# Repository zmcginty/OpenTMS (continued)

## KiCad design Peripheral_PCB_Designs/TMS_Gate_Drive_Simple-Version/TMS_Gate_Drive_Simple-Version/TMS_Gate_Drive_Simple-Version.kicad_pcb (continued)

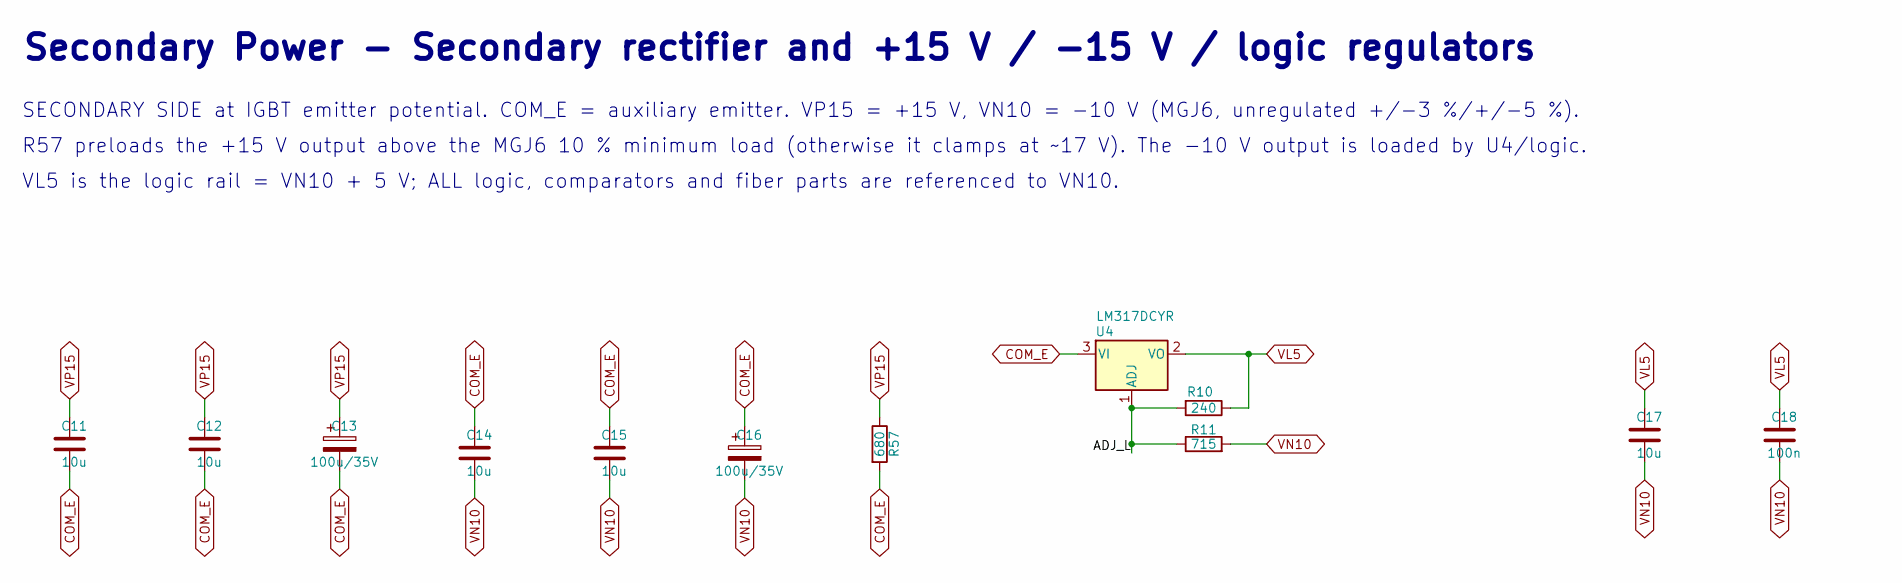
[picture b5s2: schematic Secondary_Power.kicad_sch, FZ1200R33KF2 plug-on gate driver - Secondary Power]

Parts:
C11, C12, C14, C15, C17: 10u; C_1210_3225Metric; MPN GRM32ER71H106KA12L
C13, C16: 100u/35V; CP_Elec_8x10; MPN EEE-FK1V101P
C18: 100n; C_0603_1608Metric; MPN GCM188R71H104KA57D
R10: 240; R_0603_1608Metric; MPN RC0603FR-07240L
R11: 715; R_0603_1608Metric; MPN RC0603FR-07715L
R57: 680; R_2512_6332Metric; MPN CRCW2512680RFKEG
U4: LM317DCYR; SOT-223-3_TabPin2; MPN LM317DCYR

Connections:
/Secondary_Power/ADJ_L: R10.2, R11.1, U4.1 (ADJ)
COM_E: C11.2, C12.2, C13.2, C14.1, C15.1, C16.1, R57.2, U4.3 (VI); also elsewhere on the board
VL5: C17.1, C18.1, R10.1, U4.2 (VO); also elsewhere on the board
VN10: C14.2, C15.2, C16.2, C17.2, C18.2, R11.2; also elsewhere on the board
VP15: C11.1, C12.1, C13.1, R57.1; also elsewhere on the board

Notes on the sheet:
Secondary Power - Secondary rectifier and +15 V / -15 V / logic regulators
SECONDARY SIDE at IGBT emitter potential. COM_E = auxiliary emitter. VP15 = +15 V, VN10 = -10 V (MGJ6, unregulated +/-3 %/+/-5 %).
R57 preloads the +15 V output above the MGJ6 10 % minimum load (otherwise it clamps at ~17 V). The -10 V output is loaded by U4/logic.
VL5 is the logic rail = VN10 + 5 V; ALL logic, comparators and fiber parts are referenced to VN10.

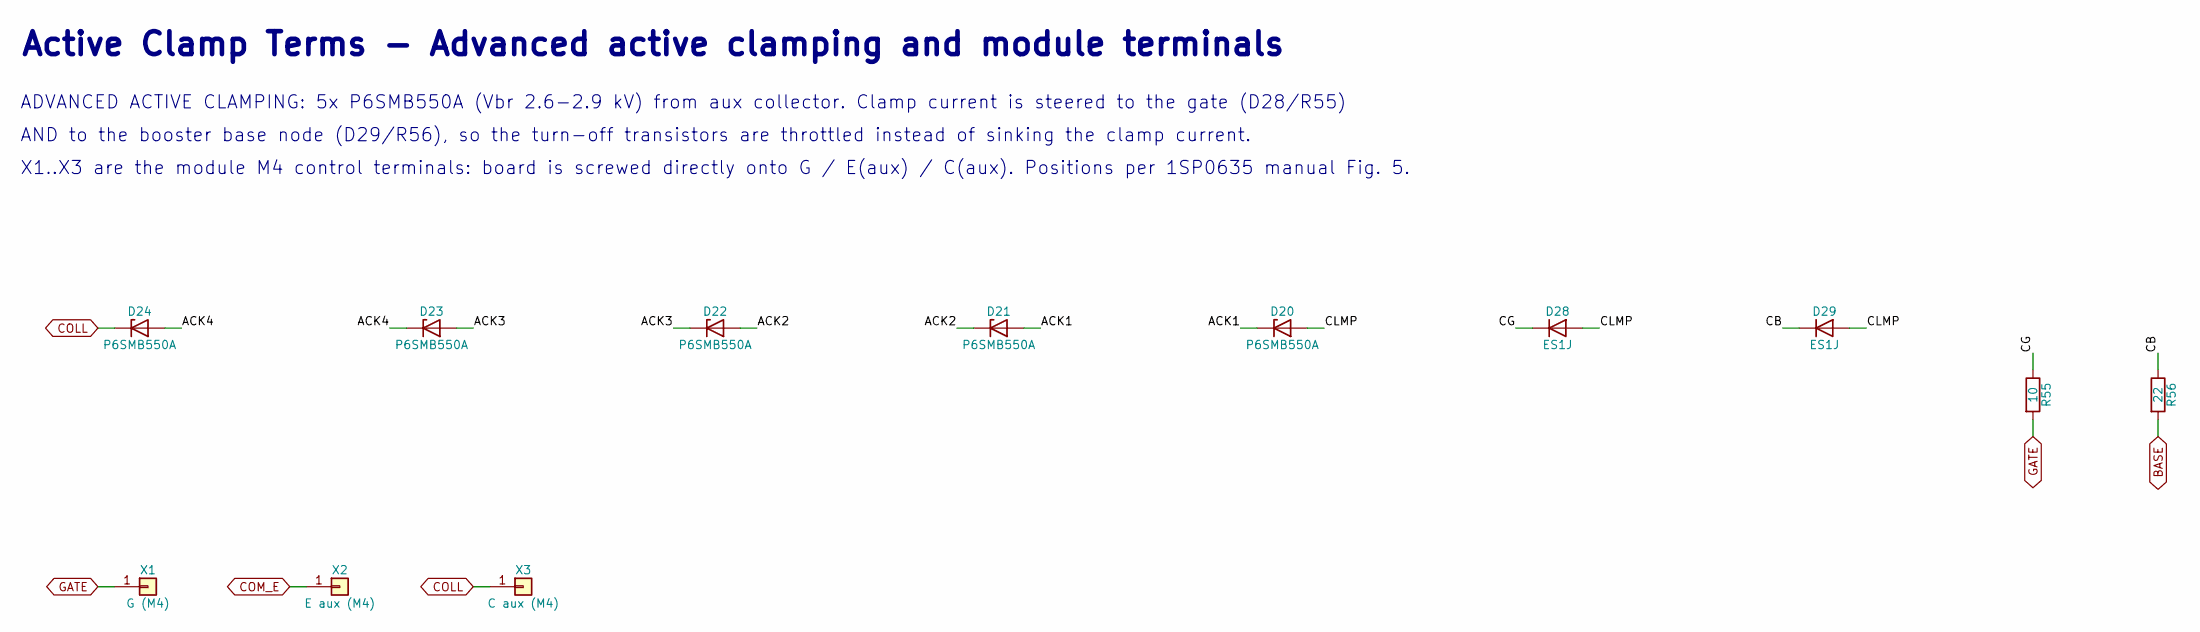
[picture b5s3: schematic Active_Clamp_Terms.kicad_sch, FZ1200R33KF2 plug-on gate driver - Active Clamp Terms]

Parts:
D20, D21, D22, D23, D24: P6SMB550A; D_SMB; MPN P6SMB550A
D28, D29: ES1J; D_SMA; MPN ES1J-E3/61T
R55: 10; R_2512_6332Metric; MPN CRCW251210R0FKEG
R56: 22; R_1206_3216Metric; MPN RC1206FR-0722L
X1: G (M4); IHV_AuxTerminal_M4; MPN M4 screw
X2: E aux (M4); IHV_AuxTerminal_M4; MPN M4 screw
X3: C aux (M4); IHV_AuxTerminal_M4; MPN M4 screw

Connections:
/Active_Clamp_Terms/ACK1: D20.1 (K), D21.2 (A)
/Active_Clamp_Terms/ACK2: D21.1 (K), D22.2 (A)
/Active_Clamp_Terms/ACK3: D22.1 (K), D23.2 (A)
/Active_Clamp_Terms/ACK4: D23.1 (K), D24.2 (A)
/Active_Clamp_Terms/CB: D29.1 (K), R56.1
/Active_Clamp_Terms/CG: D28.1 (K), R55.1
/Active_Clamp_Terms/CLMP: D20.2 (A), D28.2 (A), D29.2 (A)
BASE: R56.2; also elsewhere on the board
COLL: D24.1 (K), X3.1 (Pin_1_1); also elsewhere on the board
COM_E: X2.1 (Pin_1_1); also elsewhere on the board
GATE: R55.2, X1.1 (Pin_1_1); also elsewhere on the board

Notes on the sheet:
X1..X3 are the module M4 control terminals: board is screwed directly onto G / E(aux) / C(aux). Positions per 1SP0635 manual Fig. 5.
ADVANCED ACTIVE CLAMPING: 5x P6SMB550A (Vbr 2.6-2.9 kV) from aux collector. Clamp current is steered to the gate (D28/R55)
AND to the booster base node (D29/R56), so the turn-off transistors are throttled instead of sinking the clamp current.
Active Clamp Terms - Advanced active clamping and module terminals

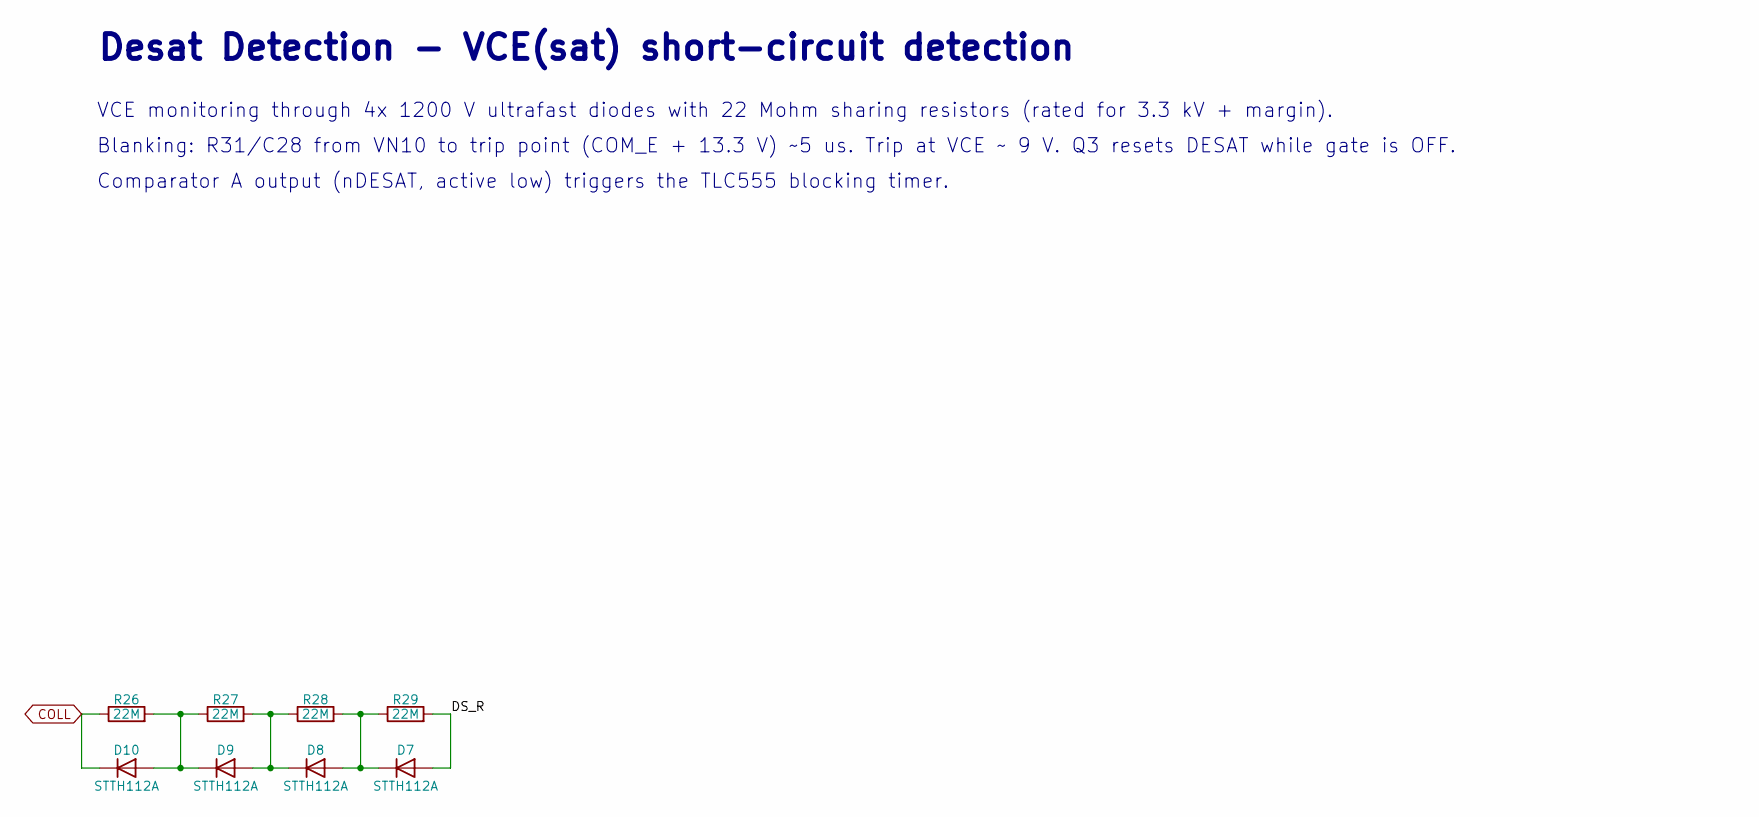
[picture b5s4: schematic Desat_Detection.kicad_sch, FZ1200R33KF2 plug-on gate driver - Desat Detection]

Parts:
D7, D8, D9, D10: STTH112A; D_SMA; MPN STTH112A
R26, R27, R28, R29: 22M; R_2512_6332Metric; MPN HVC2512T2205FET

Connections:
/Desat_Detection/DS_R: D7.2 (A), R29.2
COLL: D10.1 (K), R26.1; also elsewhere on the board
unnamed: D7.1 (K), D8.2 (A), R28.2, R29.1
unnamed: D8.1 (K), D9.2 (A), R27.2, R28.1
unnamed: D9.1 (K), D10.2 (A), R26.2, R27.1

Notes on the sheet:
Comparator A output (nDESAT, active low) triggers the TLC555 blocking timer.
VCE monitoring through 4x 1200 V ultrafast diodes with 22 Mohm sharing resistors (rated for 3.3 kV + margin).
Desat Detection - VCE(sat) short-circuit detection
Blanking: R31/C28 from VN10 to trip point (COM_E + 13.3 V) ~5 us. Trip at VCE ~ 9 V. Q3 resets DESAT while gate is OFF.

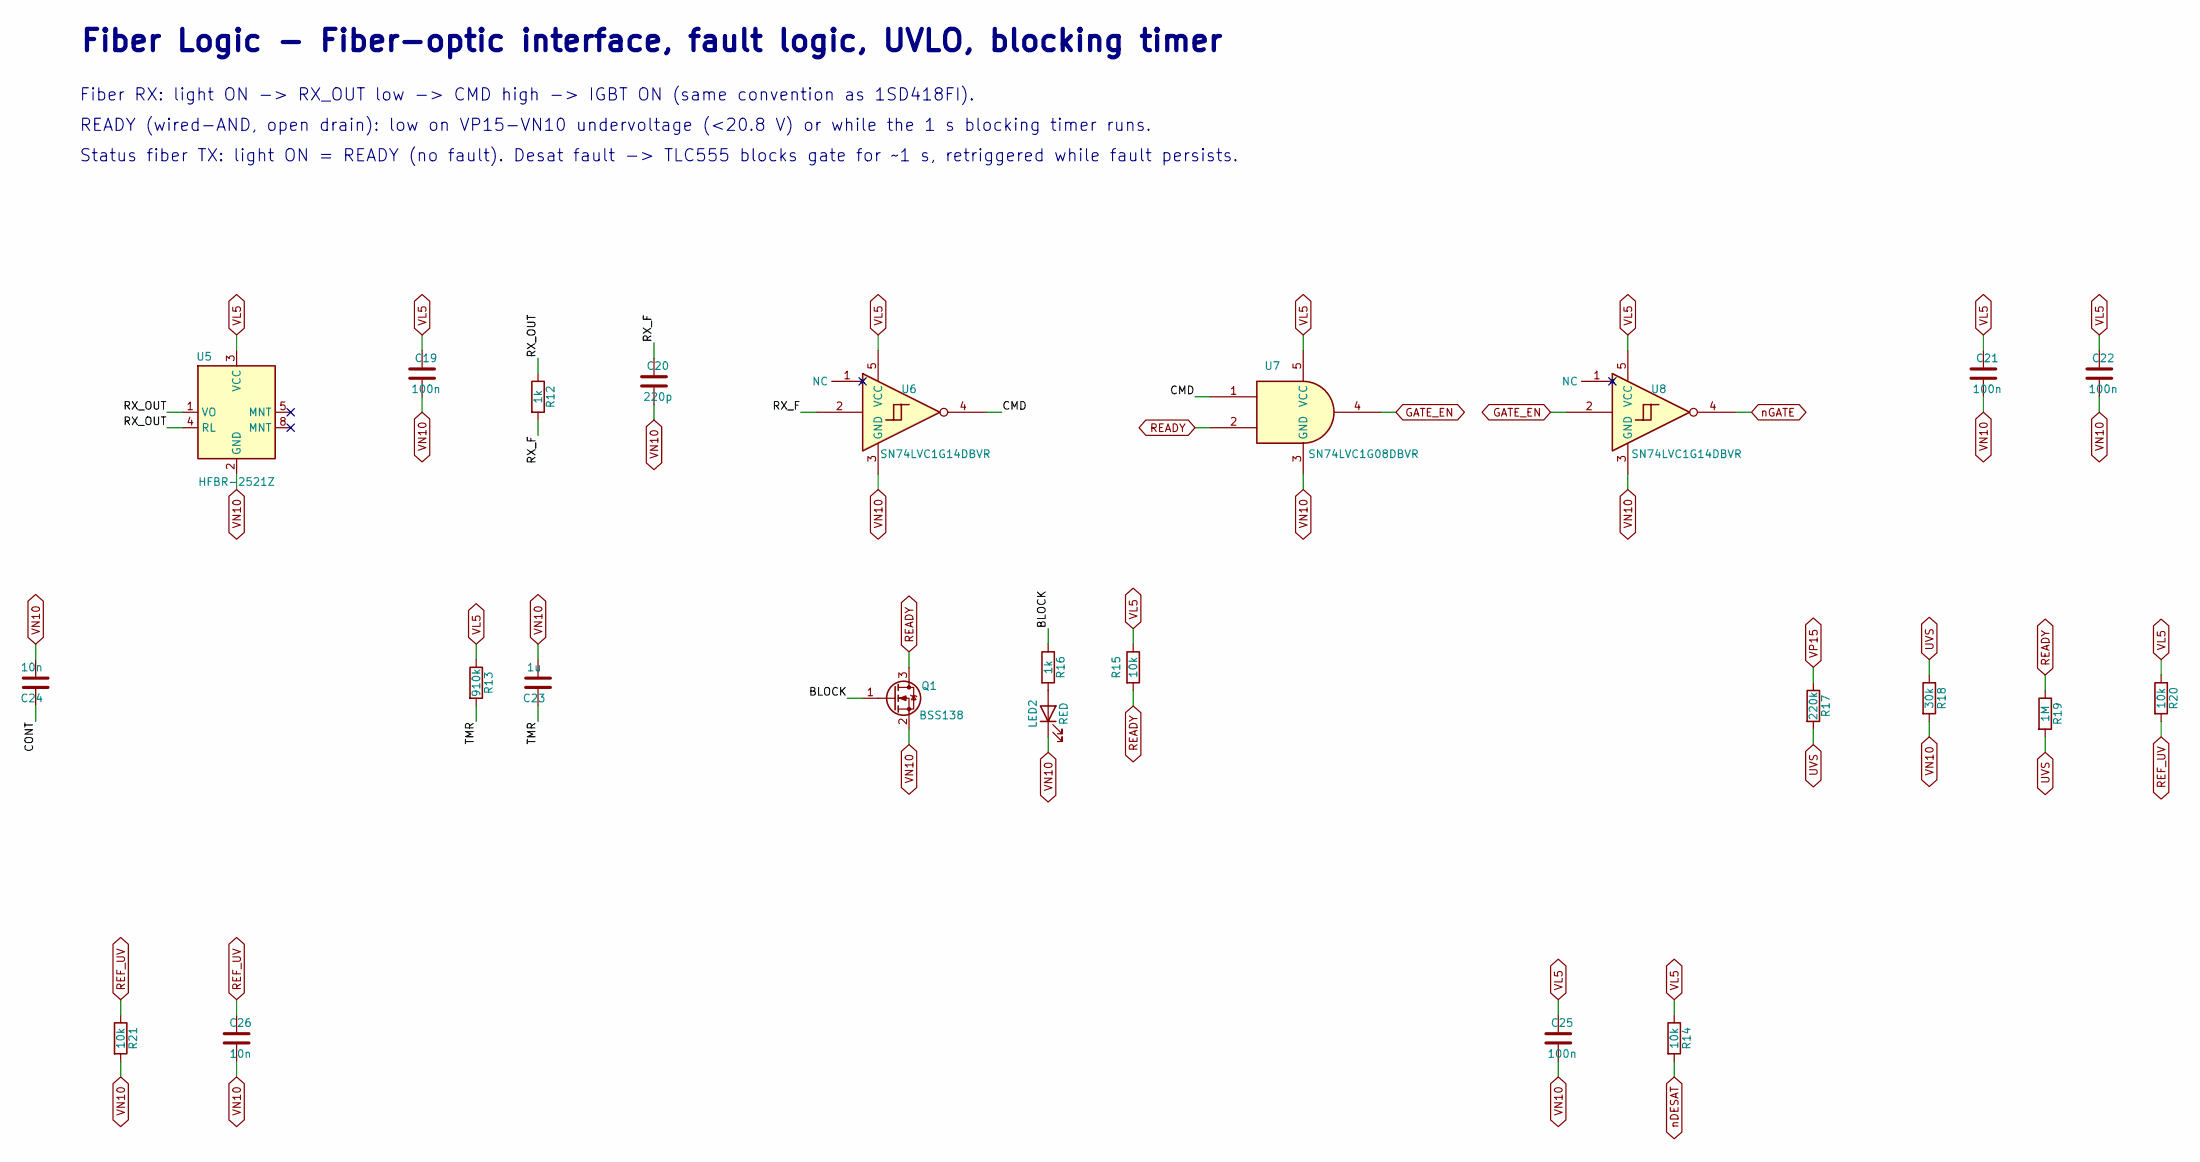
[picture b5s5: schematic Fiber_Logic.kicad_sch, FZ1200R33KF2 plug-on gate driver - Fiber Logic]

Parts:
C19, C21, C22, C25: 100n; C_0603_1608Metric; MPN GCM188R71H104KA57D
C20: 220p; C_0603_1608Metric; MPN GRM1885C1H221JA01D
C23: 1u; C_0805_2012Metric; MPN GRM21BR71H105KA12L
C24, C26: 10n; C_0603_1608Metric; MPN GCM188R71H103KA37D
LED2: RED; LED_0603_1608Metric; MPN 150060RS75000
Q1: BSS138; SOT-23; MPN BSS138
R12, R16: 1k; R_0603_1608Metric; MPN RC0603FR-071kL
R13: 910k; R_0603_1608Metric; MPN RC0603FR-07910kL
R14, R15, R20, R21: 10k; R_0603_1608Metric; MPN RC0603FR-0710kL
R17: 220k; R_0603_1608Metric; MPN RC0603FR-07220kL
R18: 30k; R_0603_1608Metric; MPN RC0603FR-0730kL
R19: 1M; R_0603_1608Metric; MPN RC0603FR-071ML
U5: HFBR-2521Z; Broadcom_VersatileLink_Horizontal; MPN HFBR-2521Z
U6, U8: SN74LVC1G14DBVR; SOT-23-5; MPN SN74LVC1G14DBVR
U7: SN74LVC1G08DBVR; SOT-23-5; MPN SN74LVC1G08DBVR

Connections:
/Fiber_Logic/BLOCK: Q1.1 (G), R16.1
/Fiber_Logic/CMD: U6.4, U7.1
/Fiber_Logic/CONT: C24.1
/Fiber_Logic/RX_F: C20.1, R12.2, U6.2
/Fiber_Logic/RX_OUT: R12.1, U5.1 (VO), U5.4 (RL)
/Fiber_Logic/TMR: C23.1, R13.2
GATE_EN: U7.4, U8.2; also elsewhere on the board
unnamed: LED2.2 (A), R16.2
READY: Q1.3 (D), R15.2, R19.1, U7.2; also elsewhere on the board
REF_UV: C26.1, R20.2, R21.1
UVS: R17.2, R18.1, R19.2
VL5: C19.1, C21.1, C22.1, C25.1, R13.1, R14.1, R15.1, R20.1, U5.3 (VCC), U6.5 (VCC), U7.5 (VCC), U8.5 (VCC); also elsewhere on the board
VN10: C19.2, C20.2, C21.2, C22.2, C23.2, C24.2, C25.2, C26.2, LED2.1 (K), Q1.2 (S), R18.2, R21.2, U5.2 (GND), U6.3 (GND), U7.3 (GND), U8.3 (GND); also elsewhere on the board
VP15: R17.1; also elsewhere on the board
nDESAT: R14.2
nGATE: U8.4

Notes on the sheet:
Status fiber TX: light ON = READY (no fault). Desat fault -> TLC555 blocks gate for ~1 s, retriggered while fault persists.
READY (wired-AND, open drain): low on VP15-VN10 undervoltage (<20.8 V) or while the 1 s blocking timer runs.
Fiber RX: light ON -> RX_OUT low -> CMD high -> IGBT ON (same convention as 1SD418FI).
Fiber Logic - Fiber-optic interface, fault logic, UVLO, blocking timer

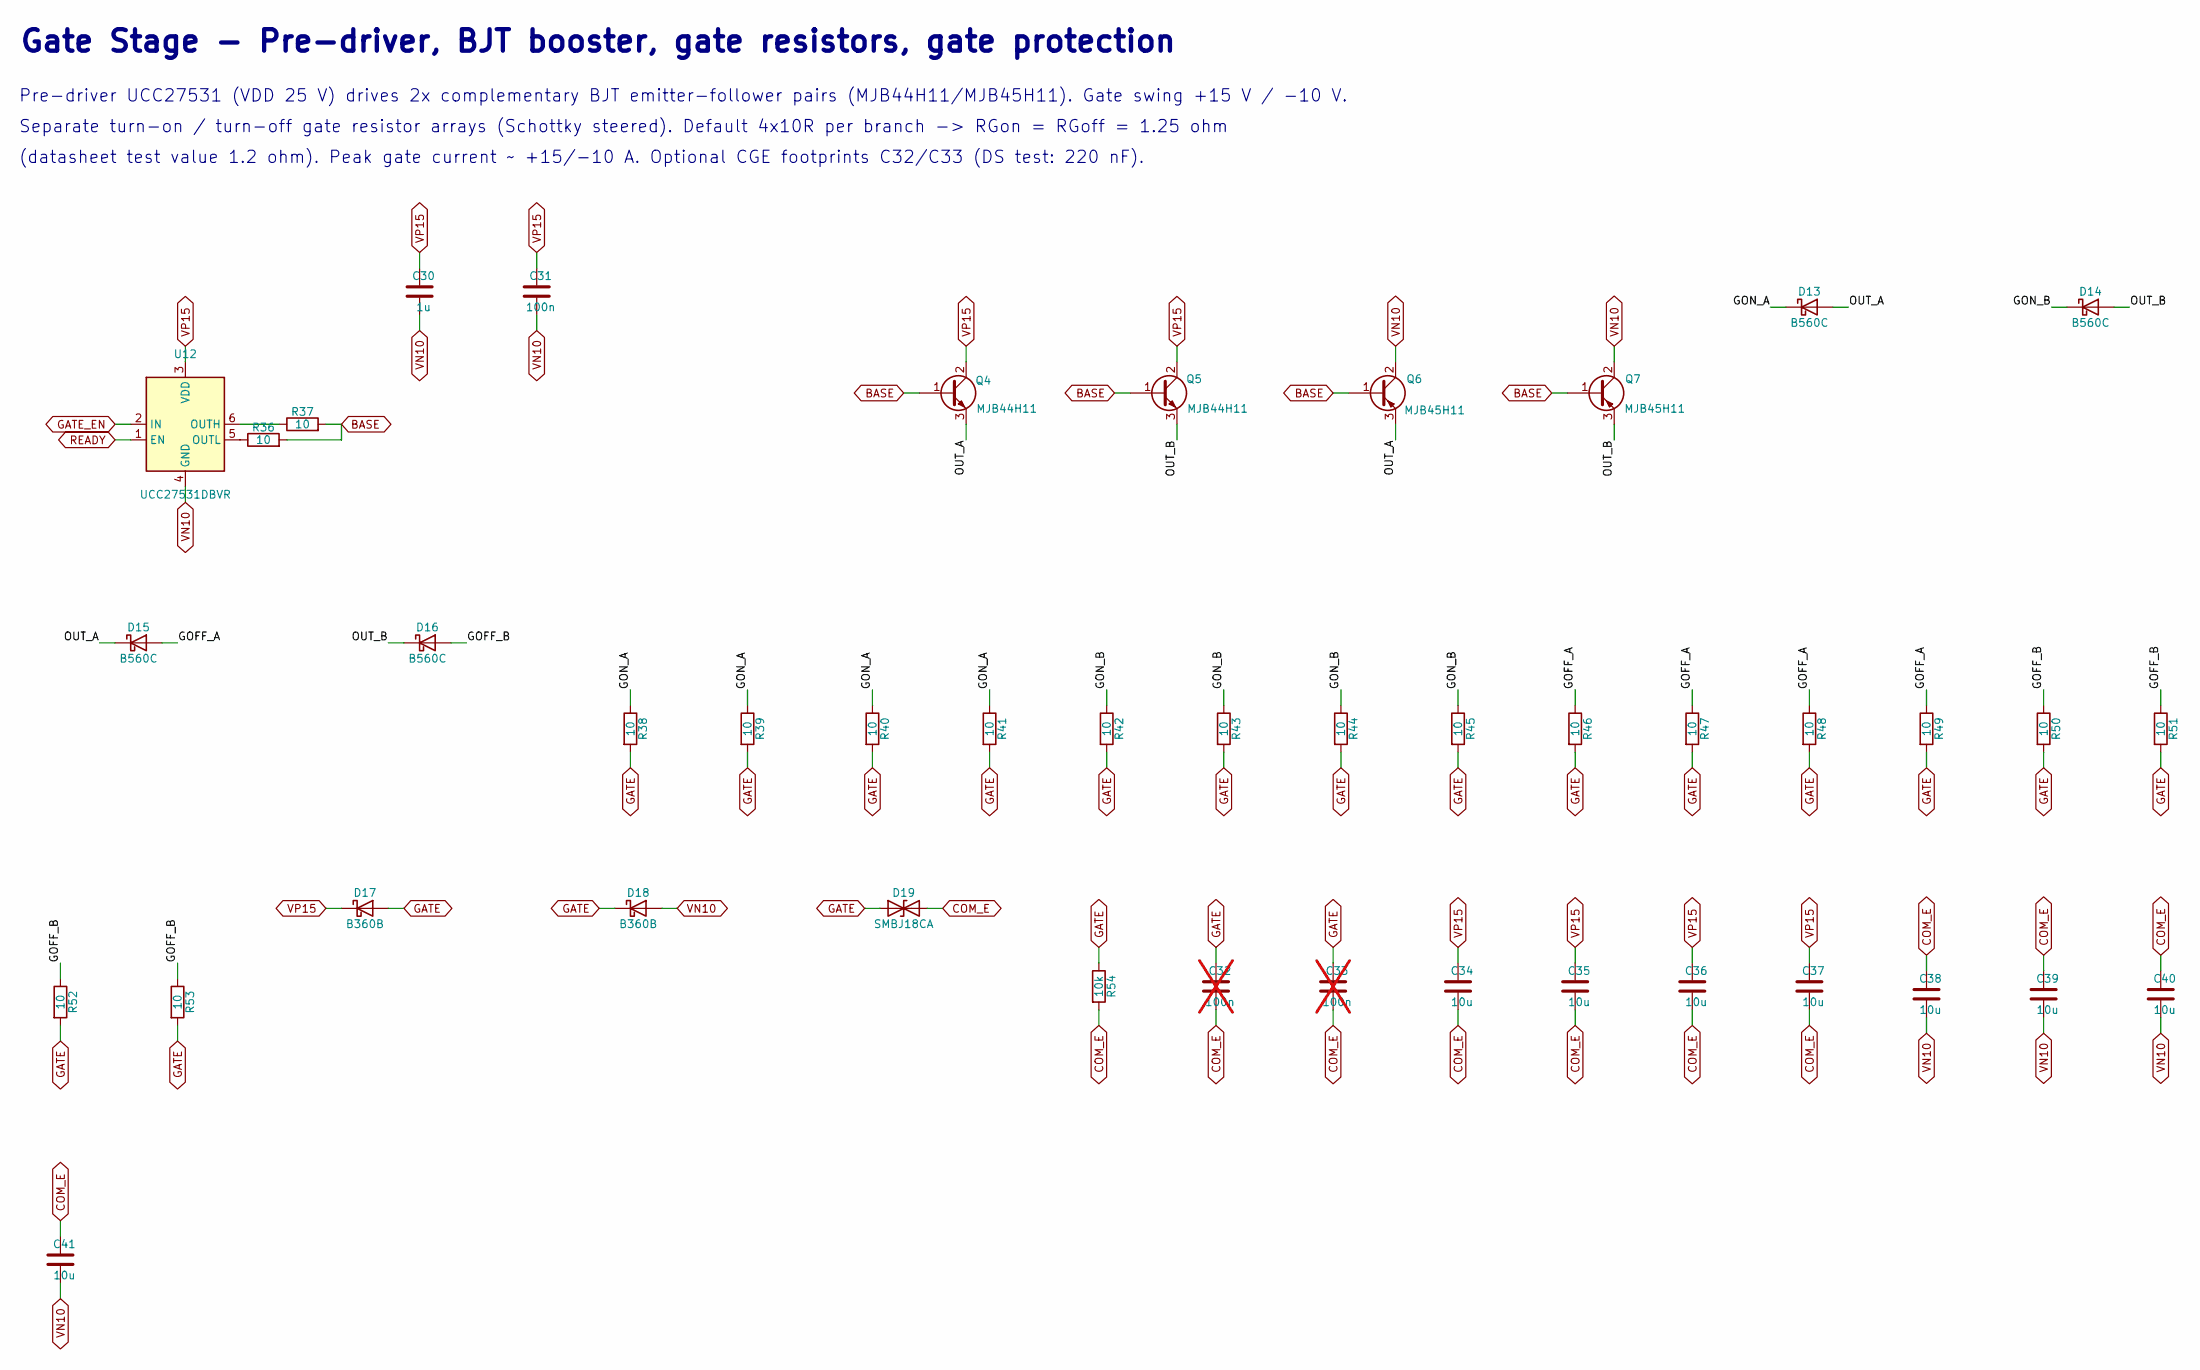
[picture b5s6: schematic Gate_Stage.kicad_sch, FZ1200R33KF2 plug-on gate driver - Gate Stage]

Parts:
C30: 1u; C_0805_2012Metric; MPN GRM21BR71H105KA12L
C31: 100n; C_0603_1608Metric; MPN GCM188R71H104KA57D
C32, C33: 100n; C_1210_3225Metric; MPN GCM32C5C1H104JA16L; not fitted
C34, C35, C36, C37, C38, C39, C40, C41: 10u; C_1210_3225Metric; MPN GRM32ER71H106KA12L
D13, D14, D15, D16: B560C; D_SMC; MPN B560C-13-F
D17, D18: B360B; D_SMB; MPN B360B-13-F
D19: SMBJ18CA; D_SMB; MPN SMBJ18CA
Q4, Q5: MJB44H11; TO-263-2; MPN MJB44H11T4G
Q6, Q7: MJB45H11; TO-263-2; MPN MJB45H11T4G
R36, R37: 10; R_1206_3216Metric; MPN RC1206FR-0710L
R38, R39, R40, R41, R42, R43, R44, R45, R46, R47, R48, R49, R50, R51, R52, R53: 10; R_2512_6332Metric; MPN CRCW251210R0FKEG
R54: 10k; R_1206_3216Metric; MPN RC1206FR-0710kL
U12: UCC27531DBVR; SOT-23-6; MPN UCC27531DBVR

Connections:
/Gate_Stage/GOFF_A: D15.2 (A), R46.1, R47.1, R48.1, R49.1
/Gate_Stage/GOFF_B: D16.2 (A), R50.1, R51.1, R52.1, R53.1
/Gate_Stage/GON_A: D13.1 (K), R38.1, R39.1, R40.1, R41.1
/Gate_Stage/GON_B: D14.1 (K), R42.1, R43.1, R44.1, R45.1
/Gate_Stage/OUT_A: D13.2 (A), D15.1 (K), Q4.3 (E), Q6.3 (E)
/Gate_Stage/OUT_B: D14.2 (A), D16.1 (K), Q5.3 (E), Q7.3 (E)
BASE: Q4.1 (B), Q5.1 (B), Q6.1 (B), Q7.1 (B), R36.2, R37.2; also elsewhere on the board
COM_E: C32.2, C33.2, C34.2, C35.2, C36.2, C37.2, C38.1, C39.1, C40.1, C41.1, D19.2 (A2), R54.2; also elsewhere on the board
GATE: C32.1, C33.1, D17.2 (A), D18.1 (K), D19.1 (A1), R38.2, R39.2, R40.2, R41.2, R42.2, R43.2, R44.2, R45.2, R46.2, R47.2, R48.2, R49.2, R50.2, R51.2, R52.2, R53.2, R54.1; also elsewhere on the board
GATE_EN: U12.2 (IN); also elsewhere on the board
unnamed: R37.1, U12.6 (OUTH)
unnamed: R36.1, U12.5 (OUTL)
READY: U12.1 (EN); also elsewhere on the board
VN10: C30.2, C31.2, C38.2, C39.2, C40.2, C41.2, D18.2 (A), Q6.2 (C), Q7.2 (C), U12.4 (GND); also elsewhere on the board
VP15: C30.1, C31.1, C34.1, C35.1, C36.1, C37.1, D17.1 (K), Q4.2 (C), Q5.2 (C), U12.3 (VDD); also elsewhere on the board

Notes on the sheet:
(datasheet test value 1.2 ohm). Peak gate current ~ +15/-10 A. Optional CGE footprints C32/C33 (DS test: 220 nF).
Pre-driver UCC27531 (VDD 25 V) drives 2x complementary BJT emitter-follower pairs (MJB44H11/MJB45H11). Gate swing +15 V / -10 V.
Gate Stage - Pre-driver, BJT booster, gate resistors, gate protection
Separate turn-on / turn-off gate resistor arrays (Schottky steered). Default 4x10R per branch -> RGon = RGoff = 1.25 ohm

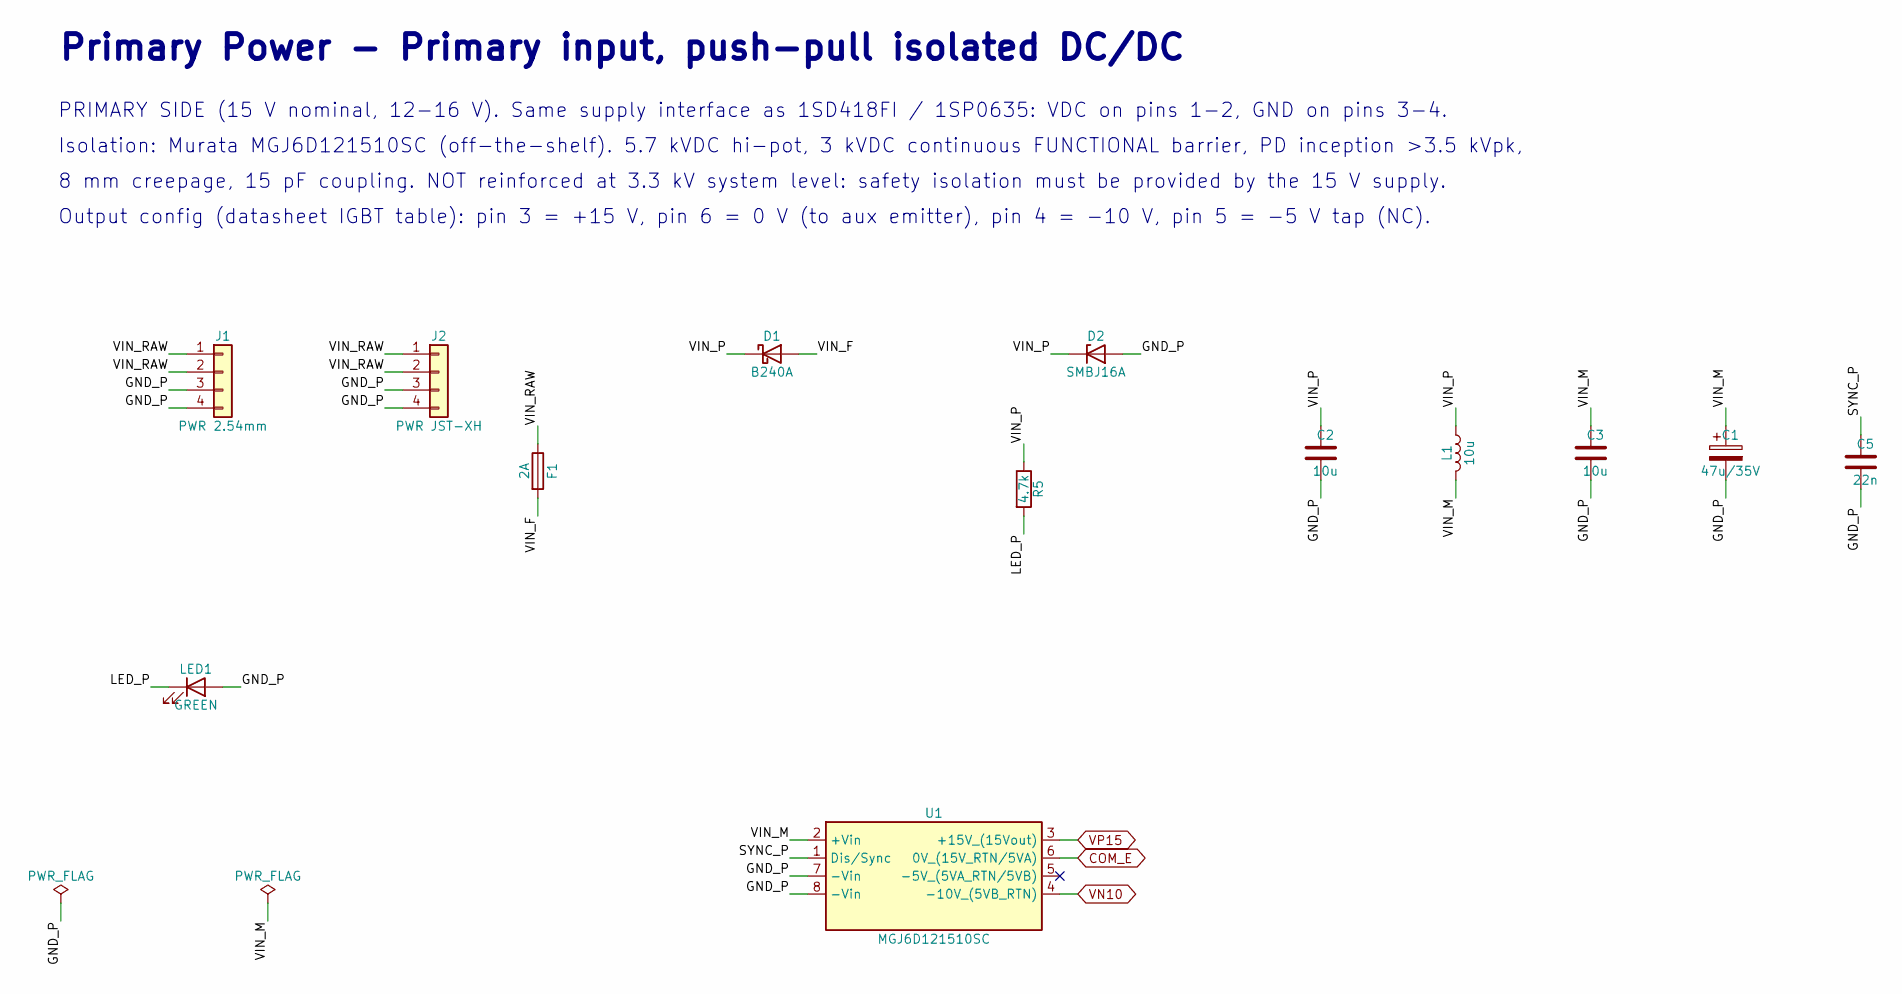
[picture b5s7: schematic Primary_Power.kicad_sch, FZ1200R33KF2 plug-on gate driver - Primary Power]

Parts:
C1: 47u/35V; CP_Elec_6.3x7.7; MPN EEE-FK1V470P
C2, C3: 10u; C_1210_3225Metric; MPN GRM32ER71H106KA12L
C5: 22n; C_0603_1608Metric; MPN GCM188R71H223KA37D
D1: B240A; D_SMA; MPN B240A-13-F
D2: SMBJ16A; D_SMB; MPN SMBJ16A
F1: 2A; Fuse_1206_3216Metric; MPN 0466002.NR
J1: PWR 2.54mm; PinHeader_1x04_P2.54mm_Vertical; MPN 61300411121
J2: PWR JST-XH; JST_XH_B4B-XH-A_1x04_P2.50mm_Vertical; MPN B4B-XH-A(LF)(SN)
L1: 10u; L_Bourns_SRN6045TA; MPN SRN6045TA-100M
LED1: GREEN; LED_0603_1608Metric; MPN 150060GS75000
R5: 4.7k; R_0603_1608Metric; MPN RC0603FR-074R7kL
U1: MGJ6D121510SC; Murata_MGJ6_SIP8; MPN MGJ6D121510SC

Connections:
/Primary_Power/GND_P: C1.2, C2.2, C3.2, C5.2, D2.2 (A), J1.3, J1.4, J2.3, J2.4, LED1.2 (A), U1.7 (-Vin), U1.8 (-Vin)
/Primary_Power/LED_P: LED1.1 (K), R5.2
/Primary_Power/SYNC_P: C5.1, U1.1 (Dis/Sync)
/Primary_Power/VIN_F: D1.2 (A), F1.2
/Primary_Power/VIN_M: C1.1, C3.1, L1.2, U1.2 (+Vin)
/Primary_Power/VIN_P: C2.1, D1.1 (K), D2.1 (K), L1.1, R5.1
/Primary_Power/VIN_RAW: F1.1, J1.1, J1.2, J2.1, J2.2
COM_E: U1.6 (0V_(15V_RTN/5VA)); also elsewhere on the board
VN10: U1.4 (-10V_(5VB_RTN)); also elsewhere on the board
VP15: U1.3 (+15V_(15Vout)); also elsewhere on the board

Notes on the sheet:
Primary Power - Primary input, push-pull isolated DC/DC
PRIMARY SIDE (15 V nominal, 12-16 V). Same supply interface as 1SD418FI / 1SP0635: VDC on pins 1-2, GND on pins 3-4.
Output config (datasheet IGBT table): pin 3 = +15 V, pin 6 = 0 V (to aux emitter), pin 4 = -10 V, pin 5 = -5 V tap (NC).
Isolation: Murata MGJ6D121510SC (off-the-shelf). 5.7 kVDC hi-pot, 3 kVDC continuous FUNCTIONAL barrier, PD inception >3.5 kVpk,
8 mm creepage, 15 pF coupling. NOT reinforced at 3.3 kV system level: safety isolation must be provided by the 15 V supply.

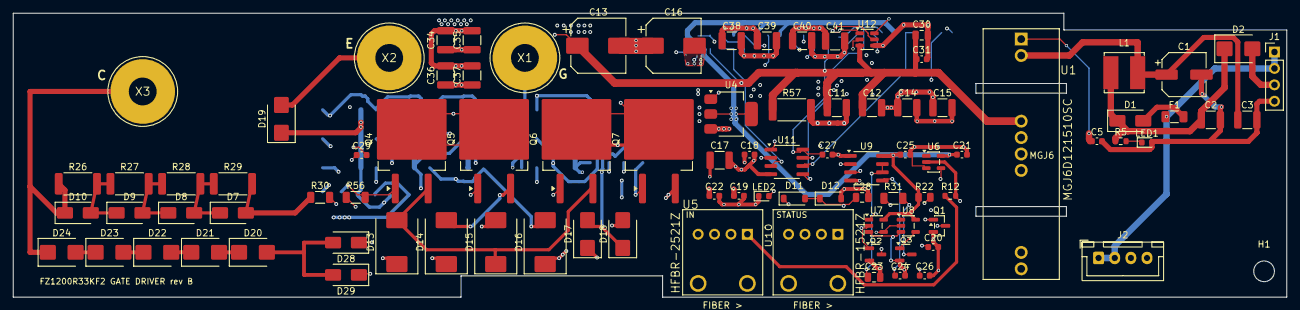
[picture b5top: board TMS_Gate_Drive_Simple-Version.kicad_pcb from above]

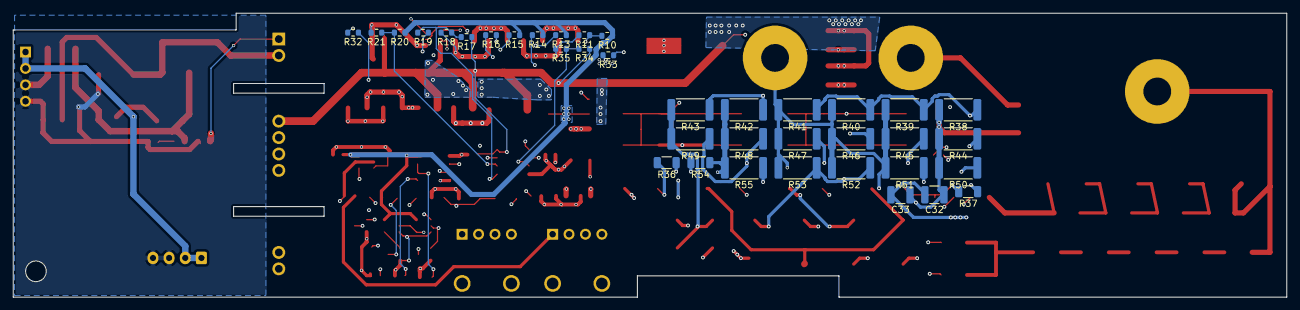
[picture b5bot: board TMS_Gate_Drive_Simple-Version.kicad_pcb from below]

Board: 4 copper layers, 197.1 x 43.9 mm, 130 parts (37 on the bottom side), 55 nets.

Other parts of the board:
C27: 100n; C_0603_1608Metric
C28: 120p; C_0805_2012Metric
C29: 10p; C_0603_1608Metric
D11, D12: BAT46W; D_SOD-123
H1: D3.2; MountingHole_3.2mm_M3
Q2, Q3: BSS138; SOT-23
R22: 120; R_0805_2012Metric
R30: 1k; R_1206_3216Metric
R31: 15k; R_1206_3216Metric
R32: 1.2M; R_0603_1608Metric
R33: 200k; R_0603_1608Metric
R34: 130k; R_0603_1608Metric
R35: 20k; R_0603_1608Metric
U9: TLC555IDR; SOIC-8_3.9x4.9mm_P1.27mm
U10: HFBR-1521Z; Broadcom_VersatileLink_Horizontal
U11: LM2903BIDR; SOIC-8_3.9x4.9mm_P1.27mm

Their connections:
/DESAT: C28.1, D11.2, D12.1, Q3.3, R30.2, R31.2, R32.1
/DREF: R34.2, R35.1, U11.3
/DSD: C29.1, R32.2, R33.1, U11.2
/READY: Q2.1, U11.7
/TMR: U9.6, U9.7
/TX_A: R22.2, U10.1
/TX_K: Q2.3, U10.2
/VL5: R22.1, U9.4, U9.8
/VN10: C27.2, C28.2, C29.2, D12.2, Q2.2, Q3.2, R33.2, R35.2, U9.1, U11.4
/VP15: C27.1, D11.1, R31.1, R34.1, U11.8
/nDESAT: U9.2, U11.1

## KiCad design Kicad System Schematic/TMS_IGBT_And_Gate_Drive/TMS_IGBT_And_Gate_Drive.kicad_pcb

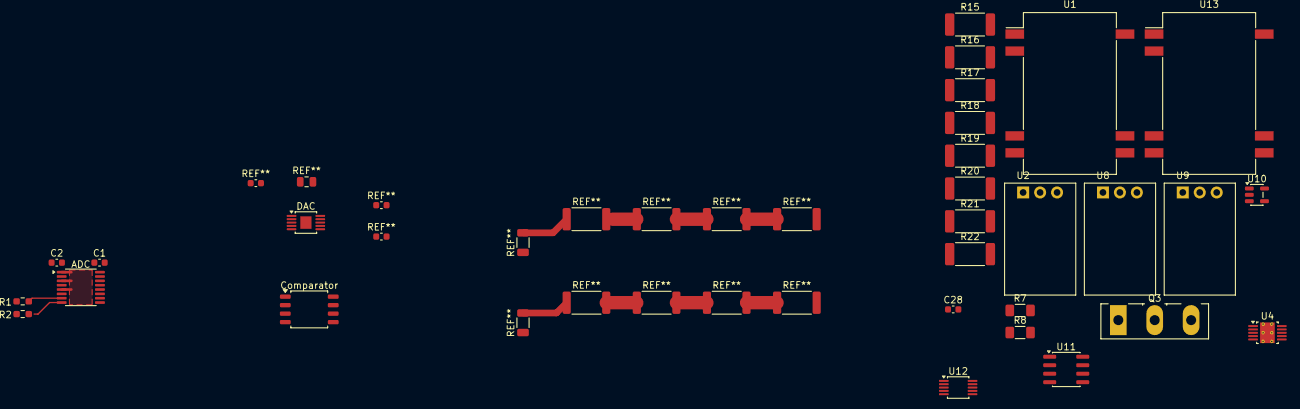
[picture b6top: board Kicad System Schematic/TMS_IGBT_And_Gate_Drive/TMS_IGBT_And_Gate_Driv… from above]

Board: 2 copper layers, 28 parts (0 on the bottom side), 15 nets.

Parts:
ADC: ADS8699IPWR; TSSOP-16_4.4x5mm_P0.65mm
C1, C2: C_0603; C_0603_1608Metric
C28: 10000p; C_0603_1608Metric
Comparator: LM293DR; SOIC-8_5.3x5.3mm_P1.27mm
DAC: AD5683RARMZ; MSOP-10-1EP_3x3mm_P0.5mm_EP1.68x1.88mm
Q3: IRG4PF50W; TO-247-3_Vertical
R1, R2: R_0603_1608Metric_Pad0.98x0.95mm_HandSolder
R7, R8: 10K; R_1206_3216Metric_Pad1.30x1.75mm_HandSolder
R15, R16, R17, R18, R19, R20, R21, R22: 1M; R_2512_6332Metric_Pad1.40x3.35mm_HandSolder
U1, U13: Isolated DC-DC Converter; Converter_DCDC_Artesyn_ATA_SMD
U2, U8, U9: Non-Isolated DC-DC Converter; Converter_DCDC_Murata_OKI-78SR_Horizontal
U4: AD5693RxRM; AD5683RARMZ
U10: MCP1415; SOT-23-5
U11: LM2931-5.0_SO8; SOIC-8_3.9x4.9mm_P1.27mm
U12: ADS1115IDGS; TSSOP-10_3x3mm_P0.5mm

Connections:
+5V: U2.3 (OUT), U8.1 (IN)
+8V: U9.3 (OUT), U11.8 (IN)
+24V: U1.16 (+VIN), U2.1 (IN), U9.1 (IN), U13.16 (+VIN)
GND: C28.2, Q3.2 (C), R7.1, R8.1, U1.1 (-VIN), U2.2 (GND), U8.2 (GND), U9.2 (GND), U11.2 (GND), U11.3 (GND), U11.6 (GND), U11.7 (GND), U12.3 (GND), U12.5 (AIN1), U12.6 (AIN2), U12.7 (AIN3), U12.8 (VDD), U13.1 (-VIN)
ISO_+15V: U1.9 (+VOUT), U10.2 (Vdd), U13.9 (+VOUT)
ISO_GND: U1.10 (-VOUT), U10.4 (GND), U13.10 (-VOUT)
unnamed: R15.2, R22.2
unnamed: R15.1, R16.2
unnamed: R16.1, R17.2
unnamed: R17.1, R18.2
unnamed: R19.2, R20.1
unnamed: R20.2, R21.1
unnamed: R21.2, R22.1
unnamed: R7.2, R19.1
unnamed: R8.2, R18.1, U12.4 (AIN0)

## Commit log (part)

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2024-11-07 added readme with simple zero-fucks description... it's a start.
2024-11-07 slightly better description of pulse-generator types.
2024-11-08 adding gitignore to ignore annoying macos files
2024-11-08 added a few basic photos of both IGBT-type and SCR-type pulse-generators, and a few photos of one oil-cooled TMS-coil
2024-11-09 adding janky schematic/layout or whatever it is for the IGBT pulse generator
2024-12-03 updated readme with basic-bitch legal CYA, and updated IGBT-based pulse-gen description.
2024-12-03 formatting
2024-12-03 added Arduino sketch which I'm using in the SCR-based TMS pulse-generator
2024-12-03 added super simple pulse generator I'm using to test IGBT-based TMS pulse-generator, this sketch has adjustments to send pulse trains
2024-12-19 wrote up some more documentation for coils (which I've been trying some new designs lately), and some general notes on charging system, and cooling systems I've found I needed to run this system at d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
2024-12-19 added photos of newest coil assembly pre and post epoxy potting, a few pictures of giant capacitors, probs a picture of my janky workbench containing TMS V3 in all it's glory. Someday..... I promise 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
2025-11-28 reorganized existing stuff into Designs #1,#2,#3, and #4 and added design #3; two-switch flyback IGBT pulse generator
